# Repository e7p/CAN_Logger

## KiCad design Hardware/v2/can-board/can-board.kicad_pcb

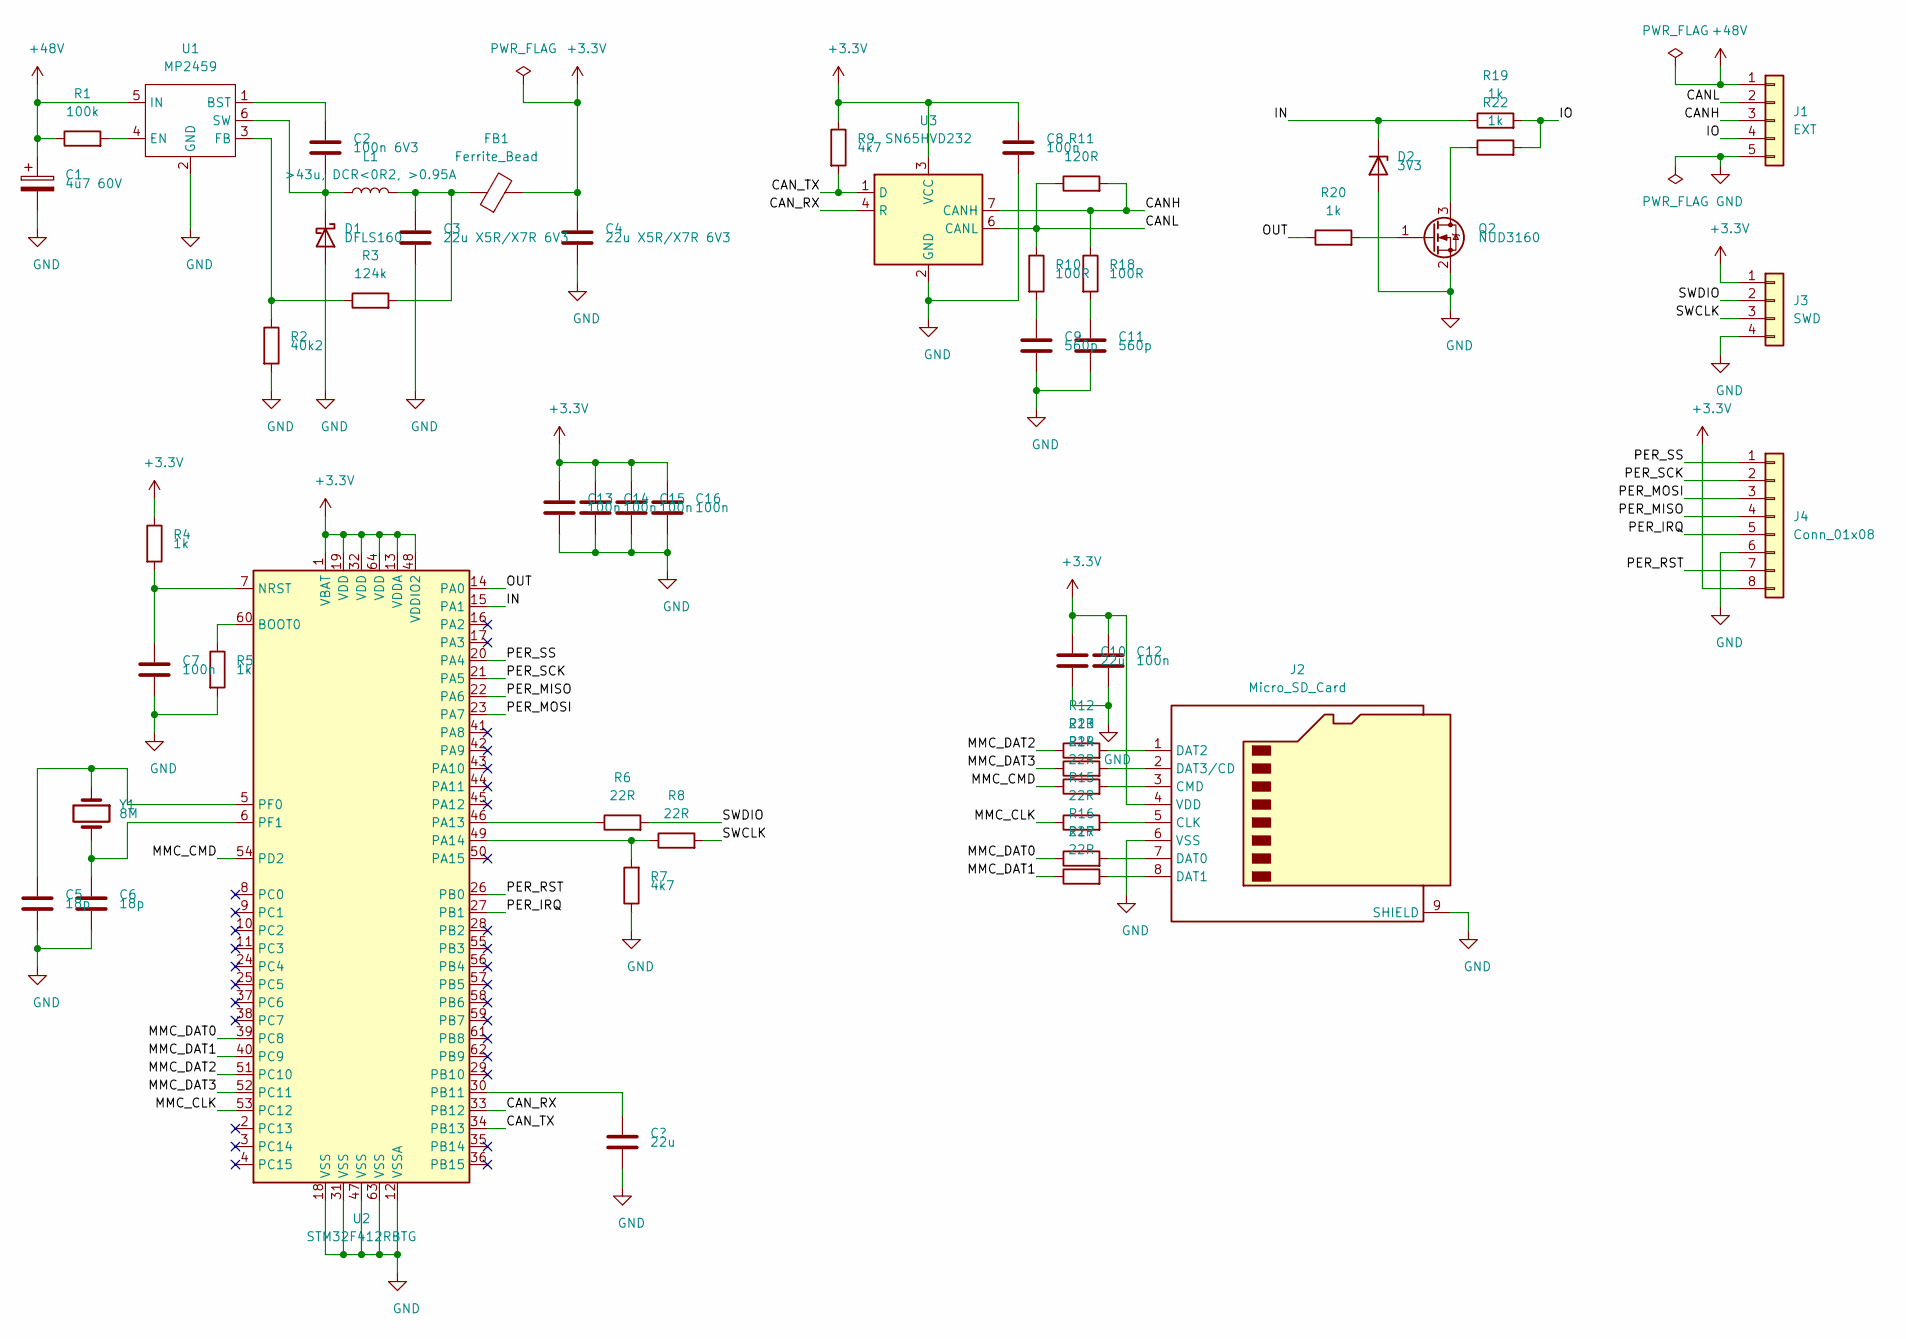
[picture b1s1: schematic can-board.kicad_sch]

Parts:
C1: 4u7 60V; CP_Radial_D5.0mm_P2.00mm
C2: 100n 6V3; C_0603_1608Metric_Pad1.05x0.95mm_HandSolder
C3, C4: 22u X5R/X7R 6V3; C_0603_1608Metric_Pad1.05x0.95mm_HandSolder
C5, C6: 18p; C_0603_1608Metric_Pad1.05x0.95mm_HandSolder
C7, C8, C12, C13, C14, C15, C16: 100n; C_0603_1608Metric_Pad1.05x0.95mm_HandSolder
C9, C11: 560p; C_0603_1608Metric_Pad1.05x0.95mm_HandSolder
C10: 22u; C_0603_1608Metric_Pad1.05x0.95mm_HandSolder
D1: DFLS160; D_PowerDI-123
D2: 3V3; D_SOD-323
FB1: Ferrite_Bead; L_0603_1608Metric_Pad1.05x0.95mm_HandSolder
J1: EXT; PinHeader_1x05_P2.54mm_Vertical
J2: Micro_SD_Card; microSD_HC_Wuerth_693072010801
J3: SWD; PinHeader_1x04_P2.54mm_Vertical
J4: Conn_01x08; PinSocket_1x08_P2.54mm_Vertical
L1: >43u, DCR<0R2, >0.95A; L_Taiyo-Yuden_NR-60xx_HandSoldering
Q2: NUD3160; SOT-23
R1: 100k; R_0603_1608Metric_Pad1.05x0.95mm_HandSolder
R2: 40k2; R_0603_1608Metric_Pad1.05x0.95mm_HandSolder
R3: 124k; R_0603_1608Metric_Pad1.05x0.95mm_HandSolder
R4, R5, R19, R20, R22: 1k; R_0603_1608Metric_Pad1.05x0.95mm_HandSolder
R6, R8, R12, R13, R14, R15, R16, R17: 22R; R_0603_1608Metric_Pad1.05x0.95mm_HandSolder
R7, R9: 4k7; R_0603_1608Metric_Pad1.05x0.95mm_HandSolder
R10, R18: 100R; R_0603_1608Metric_Pad1.05x0.95mm_HandSolder
R11: 120R; R_0603_1608Metric_Pad1.05x0.95mm_HandSolder
U1: MP2459; TSOT-23-6_HandSoldering
U2: STM32F412RBTG; LQFP-64_10x10mm_P0.5mm
U3: SN65HVD232; SOIC-8_3.9x4.9mm_P1.27mm
Y1: 8M; Crystal_SMD_HC49-SD_HandSoldering

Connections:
+3V3: C4.1, C8.1, C10.1, C12.1, C13.1, C14.1, C15.1, C16.1, FB1.2, J2.4 (VDD), J3.1, J4.8, R4.1, R9.1, U2.1 (VBAT), U2.13 (VDDA), U2.19 (VDD), U2.32 (VDD), U2.48 (VDDIO2), U2.64 (VDD), U3.3 (VCC)
+48V: C1.1, J1.1, R1.1, U1.5 (IN)
/CANH: J1.3, R11.2, R18.1, U3.7 (CANH)
/CANL: J1.2, R10.1, R11.1, U3.6 (CANL)
/CAN_RX: U2.33 (PB12), U3.4 (R)
/CAN_TX: R9.2, U2.34 (PB13), U3.1 (D)
/IN: D2.1 (K), R19.1, U2.15 (PA1)
/IO: J1.4, R19.2, R22.2
/MMC_CLK: R15.1, U2.53 (PC12)
/MMC_CMD: R14.1, U2.54 (PD2)
/MMC_DAT0: R16.1, U2.39 (PC8)
/MMC_DAT1: R17.1, U2.40 (PC9)
/MMC_DAT2: R12.1, U2.51 (PC10)
/MMC_DAT3: R13.1, U2.52 (PC11)
/OUT: R20.1, U2.14 (PA0)
/PER_IRQ: J4.5, U2.27 (PB1)
/PER_MISO: J4.4, U2.22 (PA6)
/PER_MOSI: J4.3, U2.23 (PA7)
/PER_RST: J4.7, U2.26 (PB0)
/PER_SCK: J4.2, U2.21 (PA5)
/PER_SS: J4.1, U2.20 (PA4)
/SWCLK: J3.3, R8.2
/SWDIO: J3.2, R6.2
GND: C1.2, C3.2, C4.2, C5.2, C6.2, C7.2, C8.2, C9.2, C10.2, C11.2, C12.2, C13.2, C14.2, C15.2, C16.2, D1.2 (A), D2.2 (A), J1.5, J2.6 (VSS), J2.9 (SHIELD), J3.4, J4.6, Q2.2 (S), R2.2, R5.2, R7.1, U1.2 (GND), U2.12 (VSSA), U2.18 (VSS), U2.31 (VSS), U2.47 (VSS), U2.63 (VSS), U3.2 (GND)
unnamed: C2.1, U1.1 (BST)
unnamed: C2.2, D1.1 (K), L1.1, U1.6 (SW)
unnamed: C3.1, FB1.1, L1.2, R3.2
unnamed: C5.1, U2.5 (PF0), Y1.1
unnamed: C6.1, U2.6 (PF1), Y1.2
unnamed: C7.1, R4.2, U2.7 (NRST)
unnamed: C9.1, R10.2
unnamed: C11.1, R18.2
unnamed: J2.1 (DAT2), R12.2
unnamed: J2.2 (DAT3/CD), R13.2
unnamed: J2.3 (CMD), R14.2
unnamed: J2.5 (CLK), R15.2
unnamed: J2.7 (DAT0), R16.2
unnamed: J2.8 (DAT1), R17.2
unnamed: Q2.1 (G), R20.2
unnamed: Q2.3 (D), R22.1
unnamed: R1.2, U1.4 (EN)
unnamed: R2.1, R3.1, U1.3 (FB)
unnamed: R5.1, U2.60 (BOOT0)
unnamed: R6.1, U2.46 (PA13)
unnamed: R7.2, R8.1, U2.49 (PA14)

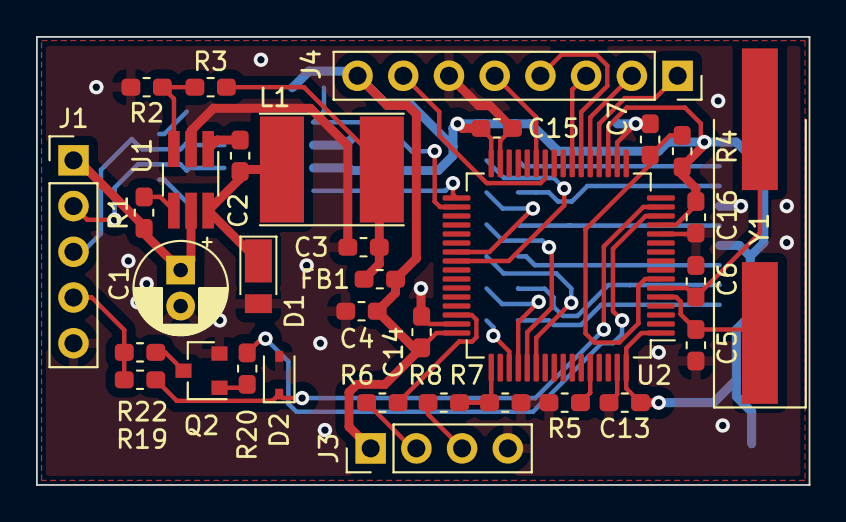
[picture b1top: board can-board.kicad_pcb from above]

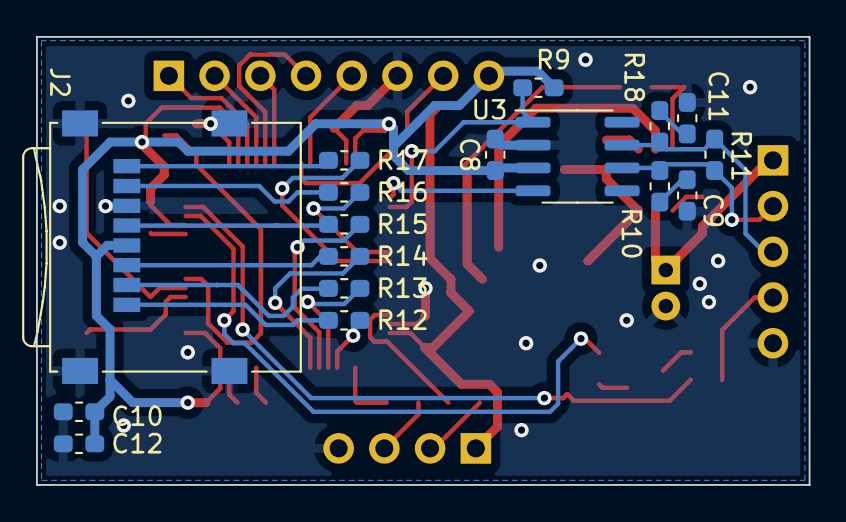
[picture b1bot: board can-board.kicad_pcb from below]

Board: 2 copper layers, 42.9 x 24.9 mm, 50 parts (17 on the bottom side), 45 nets.

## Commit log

2020-12-22 upgraded ChibiOS to 20.3.x
2021-01-03 added board.c and board.h from demo board base
2021-01-03 added second version kicad board files
2021-01-03 updated config for SD-card
